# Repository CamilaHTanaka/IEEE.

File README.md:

# IEEE.
Circuito exemplo IEEE Sanca Week

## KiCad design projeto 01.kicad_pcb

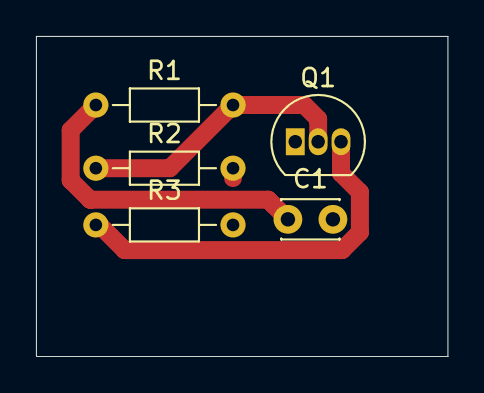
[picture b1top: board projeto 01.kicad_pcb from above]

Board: 2 copper layers, 22.9 x 17.8 mm, 5 parts (0 on the bottom side), 4 nets.

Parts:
C1: 20nF; C_Disc_D3.0mm_W2.0mm_P2.50mm
Q1: BC548; TO-92_Inline
R1: 1k; R_Axial_DIN0204_L3.6mm_D1.6mm_P7.62mm_Horizontal
R2: 510k; R_Axial_DIN0204_L3.6mm_D1.6mm_P7.62mm_Horizontal
R3: 10k; R_Axial_DIN0204_L3.6mm_D1.6mm_P7.62mm_Horizontal

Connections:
GND: R2.2, R3.2
unnamed: C1.1, R1.1
unnamed: Q1.2, R1.2, R2.1
unnamed: Q1.3, R3.1

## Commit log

2019-08-09 Esquemático do primeiro estágio
    Fio adicionado no esquemático o primeiro estágio de amplificação do circuito.
2019-08-10 Selecionei as Footprints
2019-08-10 última versão
